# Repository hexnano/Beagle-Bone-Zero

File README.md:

# Beagle-Bone-Zero
A Pi zero sized beagle bone designed by  Arsenijs, Dylan C, Ricardo, the arkadia

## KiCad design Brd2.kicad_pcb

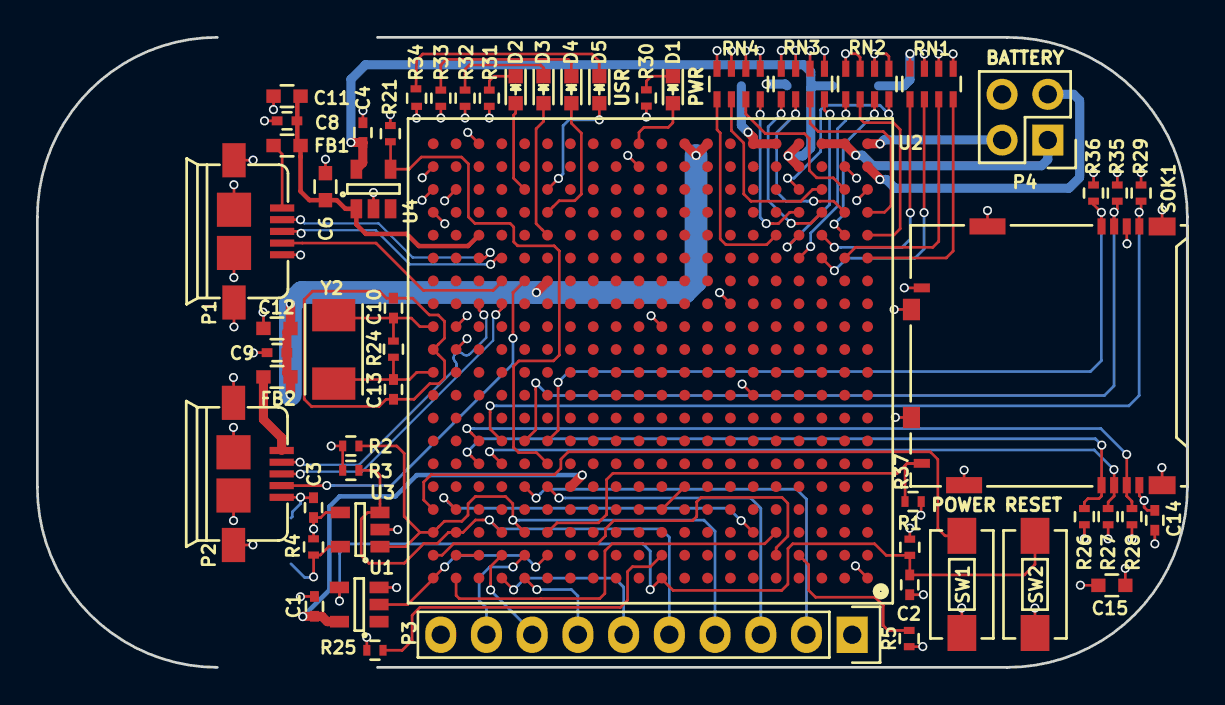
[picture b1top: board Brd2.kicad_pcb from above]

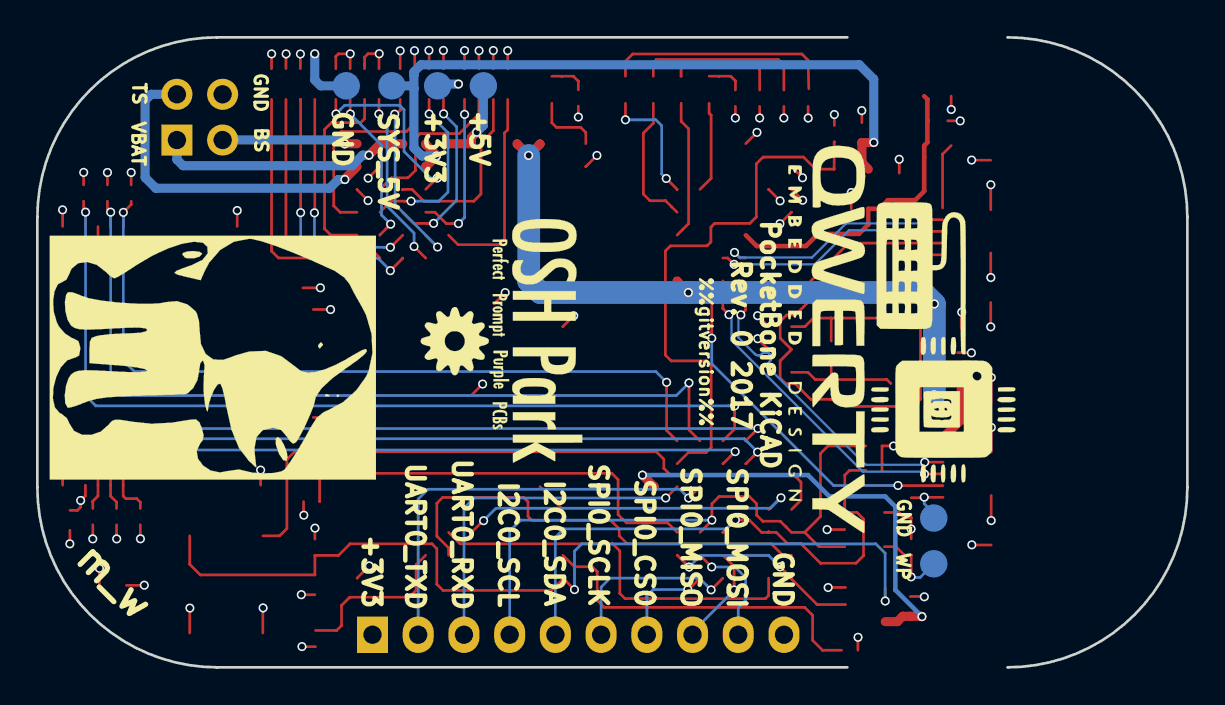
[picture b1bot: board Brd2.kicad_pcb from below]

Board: 4 copper layers, 63.9 x 35.0 mm, 62 parts (6 on the bottom side), 74 nets.

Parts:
C1, C3, C4, C8, C9, C14: 0.1uF; C_0402
C2: 1uF; C_0402
C6, C11, C12, C15: 10uF; C_0603
C10, C13: 18pF; C_0402
D1, D2, D3, D4, D5: BLUE; LED-0603
FB1, FB2: FILTER; C_0603
P1, P2: USB_OTG; USB_MICRO_B_ST-USB-001E
P3: CONN_01X10; Socket_Strip_Straight_1x10
P4: CONN_02X02; Socket_Strip_Straight_2x02
R1, R5, R26, R27, R28, R29, R35, R36, R37: 10K; R_0402
R2, R3, R4: 1.5K; R_0402
R21: 100K; R_0402
R24: 1M; R_0402
R25: 4.87K; R_0402
R30: 4.7K; R_0402
R31, R32, R33, R34: 240; R_0402
RN1, RN2, RN3, RN4: 100K; R_Array_Concave_4x0603
SOK1: SCHA5B0200
SW1, SW2: SW_PUSH_SMALL_H; SW_SPST_EVQPE1
TP1: 5V; Measurement_Point_Round-SMD-Pad_Small
TP2: WP; Measurement_Point_Round-SMD-Pad_Small
TP3, TP6: GND; Measurement_Point_Round-SMD-Pad_Small
TP4: 3P3; Measurement_Point_Round-SMD-Pad_Small
TP5: SYS_5V; Measurement_Point_Round-SMD-Pad_Small
U1: SN74LVC1G07; SOT-23-5
U2: OSD3358; BGA-400-1-27mm
U3: 24LC32AT-I/OT; SOT-23-5
U4: TPS2051C; SOT-23-5
Y2: 24MHz; 445C33D24M00000

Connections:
3P3AUX: D1.2, U2.Y11
+3V3: C3.1, C14.1, C15.1, P3.1, R1.1, R2.1, R3.1, R4.1, R26.1, R27.1, R28.1, R29.1, R35.1, R36.1, R37.1, RN2.5, RN2.6, RN2.7, RN2.8, SOK1.4, TP4.1, U2.U20, U2.V20, U3.4
+5V: TP1.1, U2.Y5, U2.Y6
BAT_SENSE: P4.3, U2.Y1
GND: C1.2, C2.2, C3.2, C4.2, C6.2, C8.2, C9.2, C11.2, C12.2, C14.2, C15.2, P1.5, P1.6, P2.5, P2.6, P3.10, P4.4, R5.2, R21.2, R25.1, R30.1, R31.1, R32.1, R33.1, R34.1, RN1.1, RN1.2, RN1.3, RN1.4, RN3.1, RN3.2, RN3.3, RN3.4, RN4.1, RN4.2, RN4.3, RN4.4, SOK1.6, SOK1.10, SOK1.11, SW1.1, SW2.1, TP3.1, TP6.1, U1.3, U2.A1, U2.J6, U2.L19, U2.M10, U2.M19, U2.N7, U2.V1, U2.V19, U2.W2, U2.W11, U2.W20, U2.Y18, U3.2, U4.2
I2C0_SCL: P3.4, R2.2, U2.C16, U2.C20, U3.1
I2C0_SDA: P3.5, R3.2, U2.C17, U2.C19, U3.3
MMC0_CD: R37.2, SOK1.9, U2.C15
MMC0_CLK: R29.2, SOK1.5, U2.G17
MMC0_CMD: R28.2, SOK1.3, U2.G18
MMC0_DAT0: R35.2, SOK1.7, U2.G16
MMC0_DAT1: R36.2, SOK1.8, U2.G15
MMC0_DAT2: R26.2, SOK1.1, U2.F18
MMC0_DAT3: R27.2, SOK1.2, U2.F17
unnamed: C2.1, R1.2, SW2.2, U1.4, U2.A10
unnamed: C10.1, R24.2, U2.M20, Y2.1
unnamed: C13.1, R24.1, U2.K20, Y2.2
unnamed: D1.1, R30.2
unnamed: D2.1, R31.2
unnamed: D3.1, R32.2
unnamed: D4.1, R33.2
unnamed: D5.1, R34.2
unnamed: FB1.2, P1.1
unnamed: FB2.2, P2.1
unnamed: R4.2, TP2.1, U3.5
unnamed: R5.1, U2.B4
unnamed: RN1.5, U2.T3
unnamed: RN1.6, U2.R3
unnamed: RN1.7, U2.R2
unnamed: RN1.8, U2.R1
unnamed: RN2.1, U2.R4
unnamed: RN2.2, U2.T1
unnamed: RN2.3, U2.T2
unnamed: RN2.4, U2.V4
unnamed: RN3.5, U2.U3
unnamed: RN3.6, U2.U2
unnamed: RN3.7, U2.U1
unnamed: RN3.8, U2.T4
unnamed: RN4.5, U2.T5
unnamed: RN4.6, U2.V3
unnamed: RN4.7, U2.V2
unnamed: RN4.8, U2.U4
unnamed: SW1.2, U2.D20
unnamed: U2.A19, U2.C5
unnamed: U2.B18, U2.B19
unnamed: U2.B5, U2.B20
unnamed: U2.C6, U2.D19
OSC0_GND: C10.2, C13.2, U2.L20
PMIC_PGOOD: U1.2, U2.A20, U2.B15
SPI_CLK: P3.6, U2.A17
SPI_CS0: P3.7, U2.A16
SPI_MISO: P3.8, U2.B17
SPI_MOSI: P3.9, U2.B16
SYS_5V: C4.1, TP5.1, U2.W4, U2.Y4, U4.5
TRSTN: R25.2, U2.B10
TS: P4.2, U2.W1
UART0_RXD: P3.3, U2.E15
UART0_TXD: P3.2, U2.E16
USB0_D_N: P2.2, U2.N18
USB0_D_P: P2.3, U2.N17
USB0_ID: P2.4, U2.P16
USB0_VBUS: C9.1, C12.1, FB2.1, U2.P15, U2.Y8, U2.Y9
USB1_DRVVBUS: R21.1, U2.F15, U4.4
USB1_D_N: P1.2, U2.R18
USB1_D_P: P1.3, U2.R17
USB1_ID: P1.4, U2.P17
USB1_VBUS: C6.1, C8.1, C11.1, FB1.1, U2.T18, U4.1
USR0_LED: D5.2, U2.V15
USR1_LED: D4.2, U2.U15
USR2_LED: D3.2, U2.T15
USR3_LED: D2.2, U2.V16
VBAT: P4.1, U2.Y2, U2.Y3
VDD_1V8: U2.D10, U2.E9
VDD_RTC: C1.1, U1.5, U2.E14
